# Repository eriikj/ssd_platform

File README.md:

ssd_platform
============

Custom digital chip for slotcars

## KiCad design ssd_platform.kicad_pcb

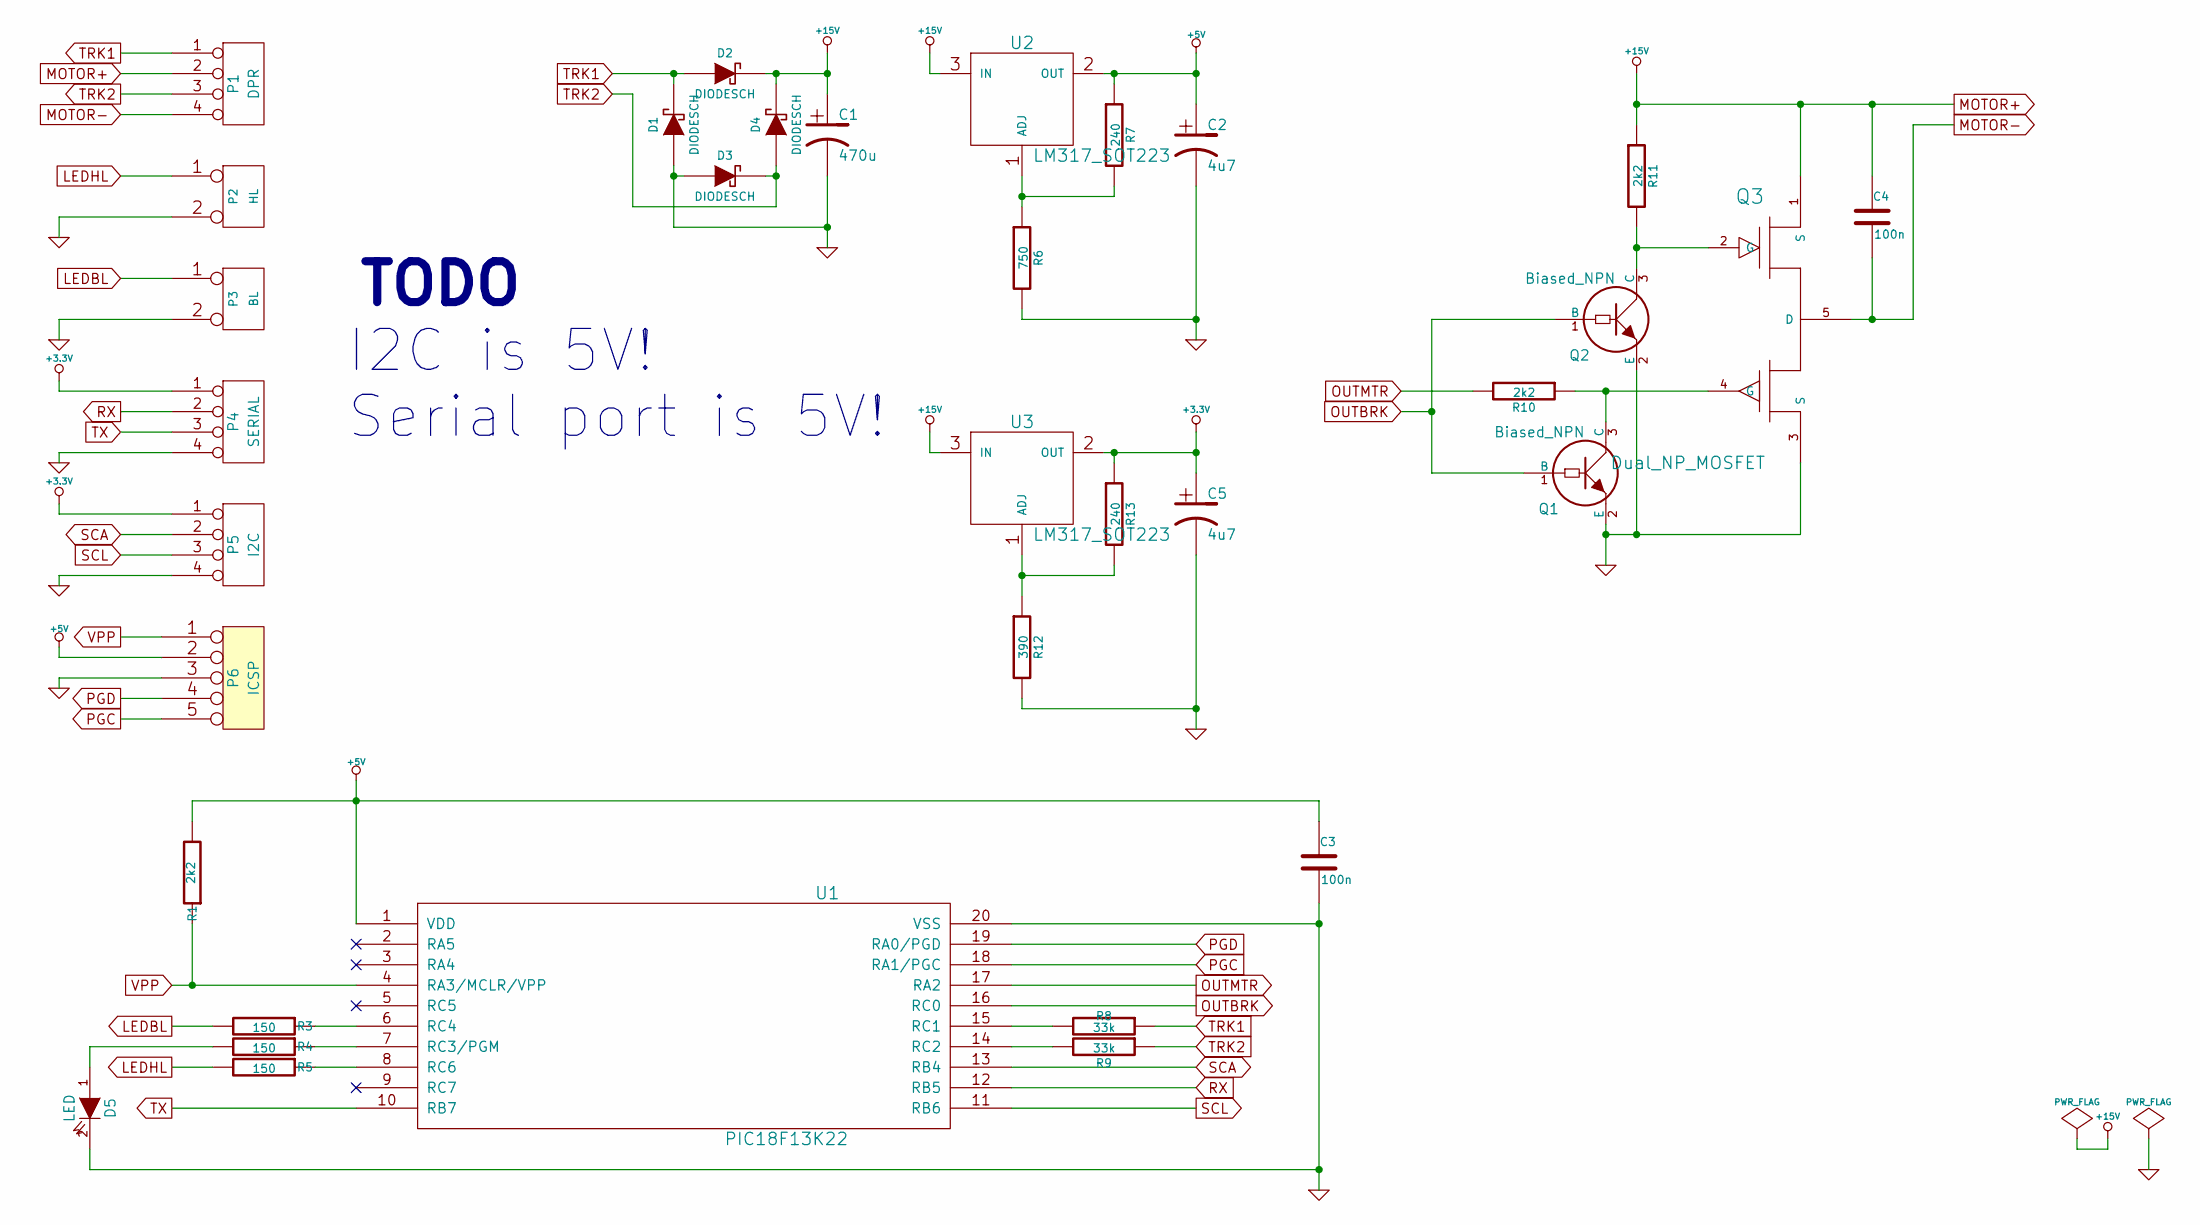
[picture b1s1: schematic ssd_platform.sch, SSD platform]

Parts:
C1: 470u
C2, C5: 4u7
C3, C4: 100n
D1, D2, D3, D4: DIODESCH
D5: LED
P1: DPR
P2: HL
P3: BL
P4: SERIAL
P5: I2C
P6: ICSP
Q1, Q2: Biased_NPN
Q3: Dual_NP_MOSFET
R1, R10, R11: 2k2
R3, R4, R5: 150
R6: 750
R7, R13: 240
R8, R9: 33k
R12: 390
U1: PIC18F13K22
U2, U3: LM317_SOT223

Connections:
+3.3V: C5.1, P4.1, P5.1, R13.1, U3.2 (OUT)
+5V: C2.1, C3.1, P6.2, R1.2, R7.1, U1.1 (VDD), U2.2 (OUT)
GND: C1.2, C2.2, C3.2, C5.2, D1.1 (A), D3.1 (A), D5.2 (K), P2.2 (PM), P3.2 (PM), P4.4, P5.4, P6.3, Q1.2 (E), Q2.2 (E), Q3.3 (S), R6.2, R12.2, U1.20 (VSS)
LEDBL: P3.1, R3.2
LEDHL: P2.1, R5.2
MOTOR+: C1.1, C4.1, D2.2 (K), D4.2 (K), P1.2, Q3.1 (S), R11.1, U2.3 (IN), U3.3 (IN)
MOTOR-: C4.2, P1.4, Q3.5 (D)
unnamed: D5.1 (A), R4.2
unnamed: Q1.3 (C), Q3.4 (G), R10.1
unnamed: Q2.3 (C), Q3.2 (G), R11.2
unnamed: R3.1, U1.6 (RC4)
unnamed: R4.1, U1.7 (RC3/PGM)
unnamed: R5.1, U1.8 (RC6)
unnamed: R6.1, R7.2, U2.1 (ADJ)
unnamed: R8.2, U1.15 (RC1)
unnamed: R9.2, U1.14 (RC2)
unnamed: R12.1, R13.2, U3.1 (ADJ)
OUTBRK: Q1.1 (B), Q2.1 (B), U1.16 (RC0)
OUTMTR: R10.2, U1.17 (RA2)
PGC: P6.5, U1.18 (RA1/PGC)
PGD: P6.4, U1.19 (RA0/PGD)
RX: P4.2, U1.12 (RB5)
SCA: P5.2, U1.13 (RB4)
SCL: P5.3, U1.11 (RB6)
TRK1: D1.2 (K), D2.1 (A), P1.1, R8.1
TRK2: D3.2 (K), D4.1 (A), P1.3, R9.1
TX: P4.3, U1.10 (RB7)
VPP: P6.1, R1.1, U1.4 (RA3/MCLR/VPP)

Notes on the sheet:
I2C is 5V! Serial port is 5V!
TODO

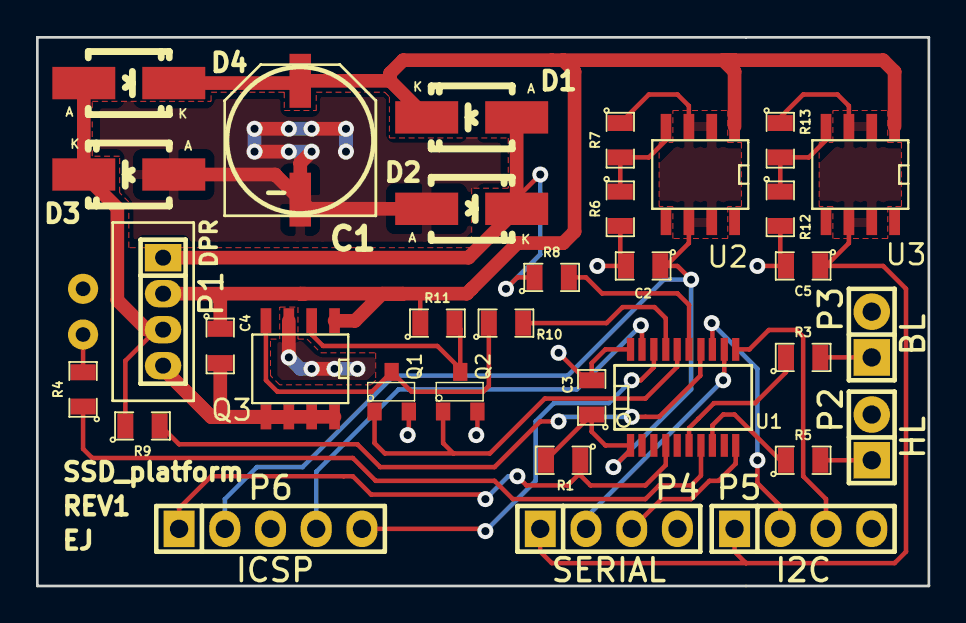
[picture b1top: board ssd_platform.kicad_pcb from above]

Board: 2 copper layers, 49.5 x 30.5 mm, 34 parts (1 on the bottom side), 28 nets.

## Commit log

2014-06-29 REV0
